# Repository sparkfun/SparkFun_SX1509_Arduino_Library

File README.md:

SparkFun SX1509 IO Expander Breakout Arduino Library
========================================

[*SparkFun SX1509 IO Expander Breakout (SKU)*](https://www.sparkfun.com/products/13601)

Arduino library for the SX1509 16-I/O expander. Capable of driving LEDs - with blink, and breathe functions - or monitoring up to 64 buttons in an 8x8 array.

Are you low on I/O? No problem! The SX1509 Breakout is a 16-channel GPIO expander with an I2C interface – that means with just two wires, your microcontroller can interface with 16 fully configurable digital input/output pins. But the SX1509 can do so much more than just simple digital pin control. It can produce PWM signals, so you can dim LEDs. It can be set to blink or even breathe pins at varying rates. This breakout is similar to a multiplexer or "mux," in that it allows you to get more IO from less pins. And, with a built-in keypad engine, it can interface with up to 64 buttons set up in an 8x8 matrix.

Two headers at the top and bottom of the breakout board function as the input and control headers to the board. This is where you can supply power to the SX1509, and where your I2C signals – SDA and SCL – will terminate. GPIO and power buses are broken out in every-which direction, and configurable jumpers cover most of the rest of the board.

Since the I/O banks can operate between 1.2V and 3.6V (5.5V tolerant) independent of both the core and each other, this device can also work as a level-shifter. The SX1509 breakout makes it easy to prototype so you can add more I/O onto your Arduino or I/O limited controller. We've even spun up an Arduino Library to get you started!

Please be aware that v3 of the library breaks previous version compatiblity on a few things:

* Wire.begin() must be called explicitly within the Arduino sketch before io.begin() is called. This may break code that does not have Wire.begin().
* io.begin() has been expanded to include io.begin(deviceAddress, wirePort, resetPin). This may break code where resetPin was the 2nd argument.

Repository Contents
-------------------

* **/examples** - Example sketches for the library (.ino). Run these from the Arduino IDE.
* **/extras** - Additional documentation for the user. These files are ignored by the IDE.
* **/src** - Source files for the library (.cpp, .h).
* **keywords.txt** - Keywords from this library that will be highlighted in the Arduino IDE.
* **library.properties** - General library properties for the Arduino package manager.

Documentation
--------------

* **[SparkFun SX1509 Breakout Board Hookup Guide](https://learn.sparkfun.com/tutorials/sx1509-io-expander-breakout-hookup-guide)** - SparkFun tutorial demonstrating how to hook up the SX1509 Breakout and use this library.
* **[Installing an Arduino Library Guide](https://learn.sparkfun.com/tutorials/installing-an-arduino-library)** - Basic information on how to install an Arduino library.
* **[Product Repository](https://github.com/sparkfun/SX1509_IO-Expander)** - Main repository (including hardware files) for the SX1509 IO Expander Breakout.

Products that use this Library
---------------------------------

* [BOB-13601](https://www.sparkfun.com/products/13601) - SX1509 16 I/O Breakout Board (v2.0)
* [BOB-11502](https://www.sparkfun.com/products/retired/11502)- (Retired) 16 I/O I2C port expander.

Version History
---------------

* [V_2.0.1](https://github.com/sparkfun/SparkFun_SX1509_Arduino_Library/tree/V_2.0.1) - Version 2.0.1. More user-friendly function calls. Increased clock functionality. More examples. Mostly backwards compatible with older versions.
* [V_1.0.0](https://github.com/sparkfun/SparkFun_SX1509_Arduino_Library/tree/V_1.0.0) - Version 1.0.0

License Information
-------------------

This product is _**open source**_!

The **code** is beerware; if you see me (or any other SparkFun employee) at the local, and you've found our code helpful, please buy us a round!

Please use, reuse, and modify these files as you see fit. Please maintain attribution to SparkFun Electronics and release anything derivative under the same license.

Distributed as-is; no warranty is given.

- Your friends at SparkFun.

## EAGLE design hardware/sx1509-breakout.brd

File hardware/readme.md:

# What Are these Files?
The .sch and .brd files hare are Eagle CAD schematic and PCB design files.

These files were created with Eagle 6.2.0, you'll need Eagle 6.0 or later to open them up. There is a free, lite, version of Eagle available from [cadsoftusa.com](http://www.cadsoftusa.com).

# Board Features

It's just a breakout board for the SX1509, but it does have its fair share of shortcuts.

## Jumpers

There are five surface mount jumpers located on the back side of the board: two to select the I<sup>2</sup>C address and two to enable the VCC1 and VCC2 rails for I/O's 0-7 and 8-15 respectively. And one jumper to disable/enable 10k pull-up resistors.

<div align="center"></div>

All jumpers are set to a default value with a small, exposed trace between the pads. With a semi-sharp exacto blade, these traces should be relatively easy to cut.

In the case of the address jumper, if you cut the trace, you'll need to apply a bubble of solder jumping the middle pad to **one** of the other two edge pads to set the ADDR pins.

### Address Jumpers

These two jumper select the I<sup>2</sup>C address of the SX1509. These jumpers allow you to select the value of the **SX1509's ADDR0 and ADDR1** pins - either VCC (1) or GND (0).

These jumpers both default to GND (0).

A table of possible values is printed on the PCB, but I'll stick it here too.

<table border="1" align="center">
<tr align="center"><td><b>ADDR1</b></td><td><b>ADDR0</b></td><td><b>SX1509 7-bit Address</b></td></b></tr>
<tr align="center"><td>0</td><td>0</td><td>0x3E</td></tr>
<tr align="center"><td>0</td><td>1</td><td>0x3F</td></tr>
<tr align="center"><td>1</td><td>0</td><td>0x70</td></tr>
<tr align="center"><td>1</td><td>1</td><td>0x71</td></tr>
</table>

### I/O Rail Jumpers

If you're looking to take advantage of the SX1509's level-shifting functionality, you may want to use the VCC1 and VCC2 pins. These pins can supply the voltage for I/O pins 0-7 and 8-15 respectively.

**Closed**, these jumpers will **short VCC1 and VCC2 to VCC** (the supply voltage 1.2-3.6V). Open the jumpers and you'll have to connect your own voltage supply. If no supply is tied to VCC1 and VCC2, the I/O pins will not work.

These jumpers **default to closed**, which means both I/O rails are tied to the supply voltage (usually 3.3V).

### Pull-up Resistor Jumpers

The SX1509 Breakout comes with 10k resistors to pull-up the I<sup>2</sup>C lines - SDA and SCL. This jumper ties both of those resistors to VCC.

The middle pad of this three-way jumper is connected to VCC. On either side is a connection to a resistor, which connects on the other end to SDA or SCL. Shorting both jumpers to VCC connects both resistors to VCC. Cutting the jumper creates an open connection on the resistor, basically removing them from the circuit.

By default, both jumpers are shorted, turning the pull-up resistors on. Should your setup require the pull-up resistors not be connected, take an exacto blade to both wire snippets.

## 2x5 Pin Headers

All I/O, power and GND pins are broken out to either side of the breakout in a breadboard-friendly manner. But 16+ wires could create quite a mess upon exiting a breadboard and entering a project. So we also made all of those 16 I/O's ribbon cable compatible.

The two 2x5 headers should mate with our [2x5 Pin Shrouded Headers](https://www.sparkfun.com/products/8506), which could mate with [Ribbon Crimp Connectors](https://www.sparkfun.com/products/10650), which could mate with [10-Wire Ribbon Cable](https://www.sparkfun.com/products/10647)!

Each of the 2x5 headers breakout out 8 I/O pins, a GND pin, and the VCC rail for that set of pins. The pinout of each connector is on the bottom of the board, but check out this picture if the bottom isn't easily visible.

<div align="center"></div>

# License
This project is released as **beerware**. Feel free to use it, with or without attribution, in your own projects. If you find it helpful, buy me a beer (alcoholic or root variety are both fine :) next time we meet up.

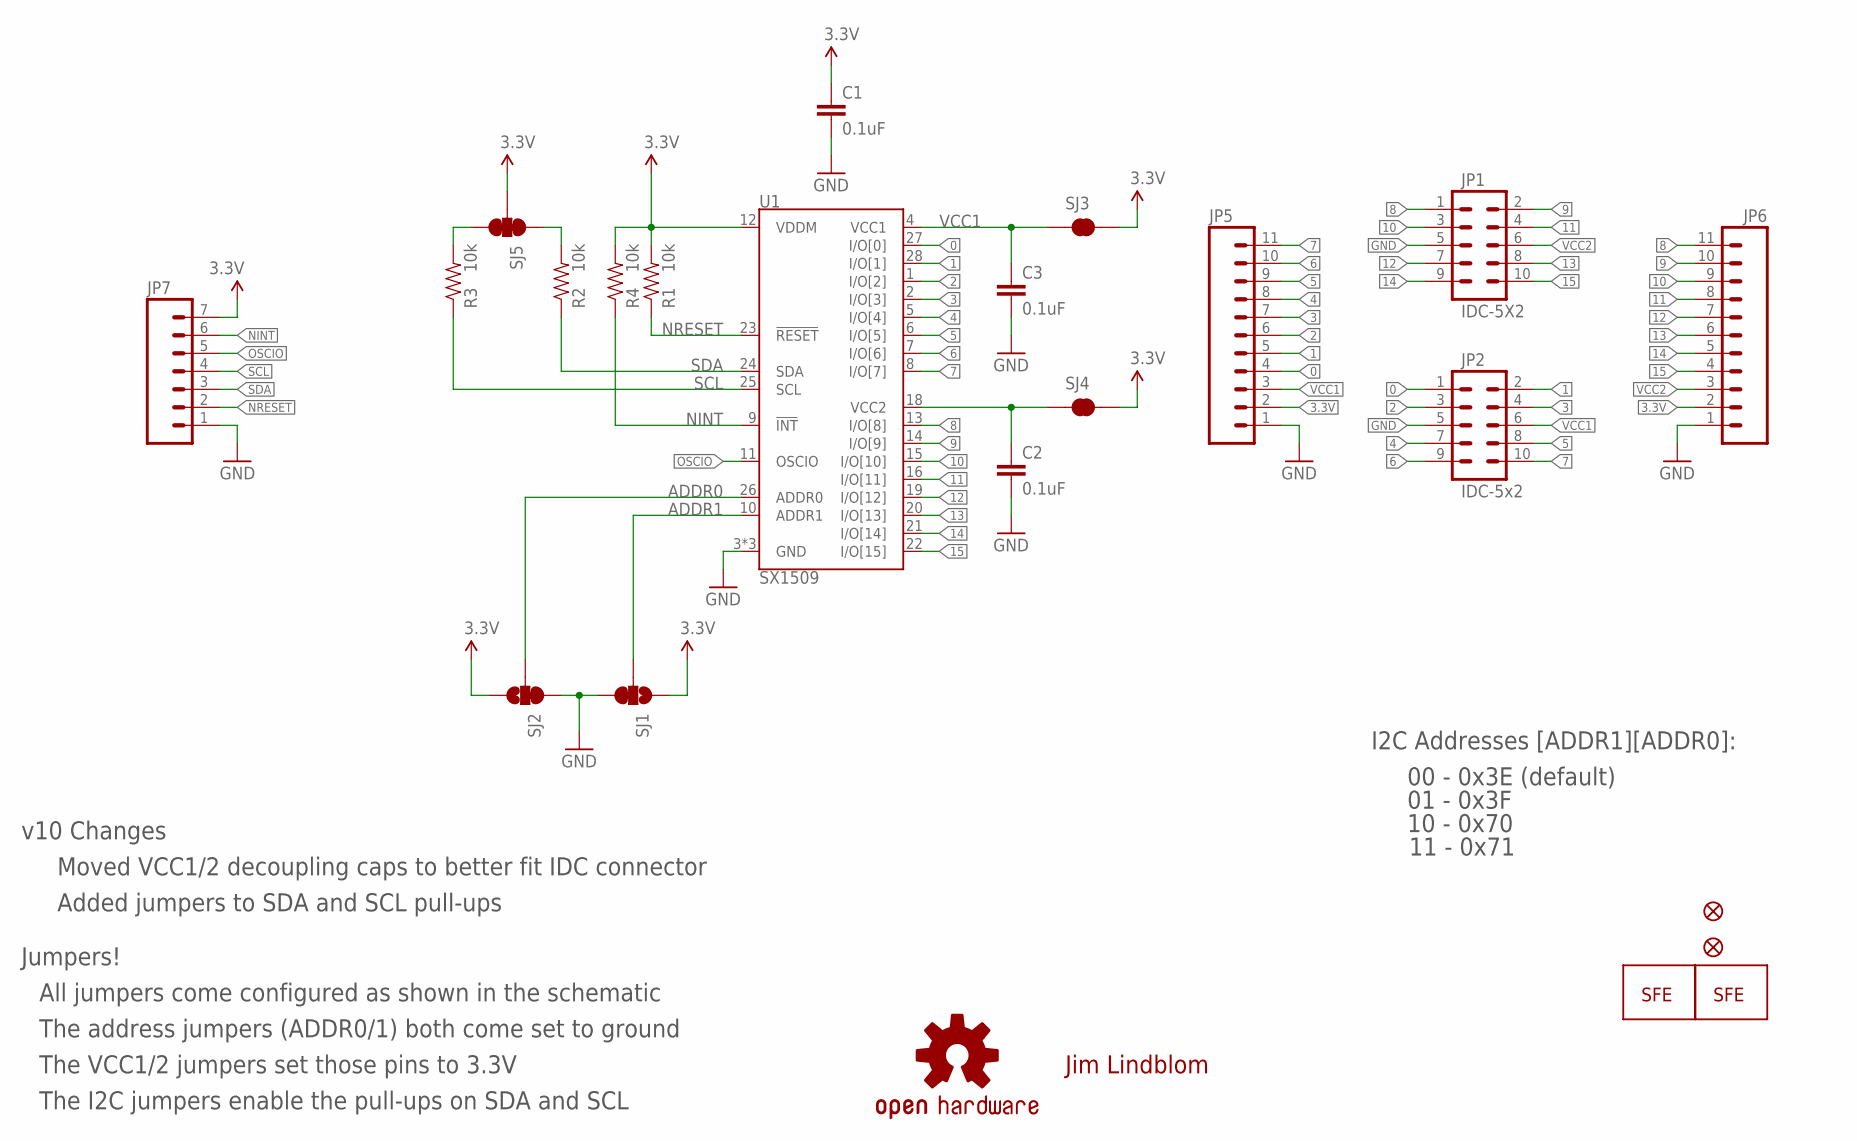
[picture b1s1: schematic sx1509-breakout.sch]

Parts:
C1, C2, C3: 0.1uF; 0402-CAP
JP1: IDC-5X2; 2X5-SHROUDED-NO_SILK
JP2: IDC-5x2; 2X5-SHROUDED-NO_SILK
JP3: LOGO-SFENEW; SFE-NEW-WEBLOGO
JP4: LOGO-SFESK; SFE-LOGO-FLAME
JP5, JP6: M111X11_NO_SILK; 1X11_NO_SILK
JP7: M07; 1X07
JP8, JP9: FIDUCIALUFIDUCIAL; MICRO-FIDUCIAL
R1, R2, R3, R4: 10k; 0402-RES
SJ1, SJ2, SJ5: SOLDERJUMPER_2WAYS; SJ_3
SJ3, SJ4: SOLDERJUMPERNO; SJ_2S-NO
U1: SX1509; QFN-28
U$1: OSHW-LOGOS; OSHW-LOGO-S

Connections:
0: JP2.1, JP5.4, U1.27 (I/O[0])
1: JP2.2, JP5.5, U1.28 (I/O[1])
2: JP2.3, JP5.6, U1.1 (I/O[2])
3: JP2.4, JP5.7, U1.2 (I/O[3])
3.3V: C1.1, JP5.2, JP6.2, JP7.7, R1.2, R4.2, SJ1.1, SJ2.3, SJ3.2, SJ4.2, SJ5.2, U1.12 (VDDM)
4: JP2.7, JP5.8, U1.5 (I/O[4])
5: JP2.8, JP5.9, U1.6 (I/O[5])
6: JP2.9, JP5.10, U1.7 (I/O[6])
7: JP2.10, JP5.11, U1.8 (I/O[7])
8: JP1.1, JP6.11, U1.13 (I/O[8])
9: JP1.2, JP6.10, U1.14 (I/O[9])
10: JP1.3, JP6.9, U1.15 (I/O[10])
11: JP1.4, JP6.8, U1.16 (I/O[11])
12: JP1.7, JP6.7, U1.19 (I/O[12])
13: JP1.8, JP6.6, U1.20 (I/O[13])
14: JP1.9, JP6.5, U1.21 (I/O[14])
15: JP1.10, JP6.4, U1.22 (I/O[15])
ADDR0: SJ2.2, U1.26 (ADDR0)
ADDR1: SJ1.2, U1.10 (ADDR1)
GND: C1.2, C2.2, C3.2, JP1.5, JP2.5, JP5.1, JP6.1, JP7.1, SJ1.3, SJ2.1, U1.3 (GND), U1.17 (GND), U1.29 (GND)
unnamed: R3.2, SJ5.3
unnamed: R2.2, SJ5.1
NINT: JP7.6, R4.1, U1.9 (!INT)
NRESET: JP7.2, R1.1, U1.23 (!RESET)
OSCIO: JP7.5, U1.11 (OSCIO)
SCL: JP7.4, R3.1, U1.25 (SCL)
SDA: JP7.3, R2.1, U1.24 (SDA)
VCC1: C3.1, JP2.6, JP5.3, SJ3.1, U1.4 (VCC1)
VCC2: C2.1, JP1.6, JP6.3, SJ4.1, U1.18 (VCC2)

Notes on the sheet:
Jim Lindblom
Jumpers!
v10 Changes
Moved VCC1/2 decoupling caps to better fit IDC connector
Added jumpers to SDA and SCL pull-ups
All jumpers come configured as shown in the schematic
The address jumpers (ADDR0/1) both come set to ground
The VCC1/2 jumpers set those pins to 3.3V
The I2C jumpers enable the pull-ups on SDA and SCL
I2C Addresses [ADDR1][ADDR0]:
00 - 0x3E (default)
01 - 0x3F
10 - 0x70
11 - 0x71

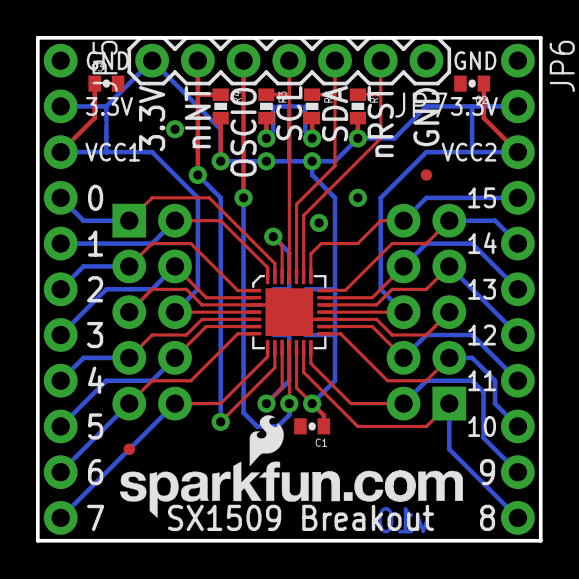
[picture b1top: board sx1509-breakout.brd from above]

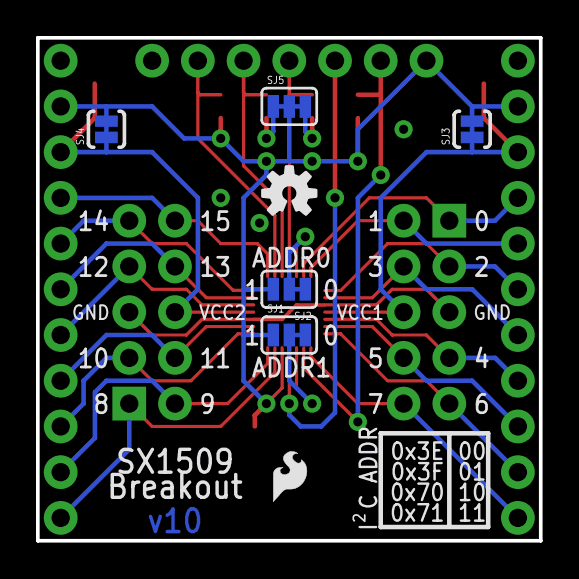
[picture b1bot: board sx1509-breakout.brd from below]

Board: 2 copper layers, 27.9 x 27.9 mm, 23 parts (7 on the bottom side), 29 nets.

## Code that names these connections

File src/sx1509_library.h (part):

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// Inputs:
//		- address: should be the 7-bit address of the SX1509. This should be  
//		 one of four values - 0x3E, 0x3F, 0x70, 0x71 - all depending on what the
//		 ADDR0 and ADDR1 pins ar se to. This variable is required.
//		- resetPin: This is the Arduino pin tied to the SX1509 RST pin. This
//		 pin is optional. If not declared, the library will attempt to
//		 software reset the SX1509.
//		- interruptPin: This is the Arduino pin tied to the SX1509 active-low
//		 interrupt output. Only necessary if you're planning on using
//		 the interrupt capabilities.
//		- oscillatorPin: This is the Arduino pin tied to the SX1509's OSCIO 
//		 pin. This pin can be an output or an input. This parameter is optional.
// -----------------------------------------------------------------------------
	sx1509Class(byte address, byte resetPin = 255, 
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// -----------------------------------------------------------------------------
// sync(void): this function resets the PWM/Blink/Fade counters, syncing any 
//		blinking LEDs. Bit 2 of REG_MISC is set, which alters the functionality 
//		of the nReset pin. The nReset pin is toggled low->high, which should 
//		reset all LED counters. Bit 2 of REG_MISC is again cleared, returning 
//		nReset pin to POR functionality
// -----------------------------------------------------------------------------
	void sync(void);
	
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//
//	Inputs:
//	- oscSource: Choose either internal 2MHz oscillator or an external signal 
//		applied to the OSCIO pin.
//		- INTERNAL_CLOCK and EXTERNAL_CLOCK are defined in the header file.
//			Use those.
//		- This value defaults to internal.
//	- oscPinFunction: Allows you to set OSCIO as an input or output.
//		- You can use Arduino's INPUT, OUTPUT defines for this value
//		- This value defaults to input
//	- oscFreqOut: If oscio is configured as an output, this will set the output 
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
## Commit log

2012-11-14 Hardware initial commit
    and a readme
2012-11-14 Library initial commit
    Working example code for init, pinDir, writePin, and readPin.
2012-11-15 Added much LED Driver functionality
    New Functions: ledDriverInit, pwm, blink, sync
    New example to demo LED driver
    Renamed simple example
2012-11-16 Debounce, interrupt and clock config functions
    Added a new example sx1509_interruptDebounce.ino
    Fixed some directory structure with examples
    Typo on a register in sx1509_registers.h
    Added keywords.txt (doesn't seem to work...hmm)
2012-11-20 Keypad engine functions and arduino example
    Added keypad(byte rows, byte columns, byte sleepTime, byte scanTime) and
    nsigned int readKeyData() to sx1509Class
2012-12-13 Comments! Licenses!
    Moved function explanation comments to the sx1509_library.h.
    Slight changes to the digitalReadWrite example.
2013-01-03 Readme goodness.
    Also removed a duplicate sx1509_ledDriver.ino and its folder.
2013-01-04 Some hardware readme action.
2013-03-08 purging HTML, adding license info and standard image/link setup
2015-04-24 Revising file structure to match Arduino 1.6 standards.
2015-04-24 Revising README.md
2015-09-08 Adding sink flag to ledDriverInit
2015-09-08 Updating file and library names to match SparkFun guidelines
2015-09-08 Fixing library name in properties file (no slashes allowed)
2015-09-21 Updating to version 2.0 - more user-friendly
    - Made most functions more user friendly.
    - digitalWrite, pinMode, and other standard Arduino function calls are
    used.
    - Should remain mostly backwards compatible.
    - blink and breathe functions now try to estimate millisecond durations
    - Improved clock control
2015-09-23 Updating README for hardware v20
2015-09-25 Reverting library name
2015-09-25 Pointing to tag V_2.0.1
2017-06-25 Remove unused variable in function readBytes
    The results of Wire.read() are directly placed into an array passed as a function variable. The variable may have been used previously, but now is not.
2017-06-25 Update SparkFunSX1509.cpp
    The results of Wire.read() are directly placed into an array passed as a function variable. The variable may have been used previously, but now is not.
2017-06-25 Issue #2
    No need to wait for data after Wire.requestFrom() #2
2018-07-15 Correct case of reference link in keywords.txt
    The third field of keywords.txt is used to provide Arduino Language/Libraries Reference links, which are accessed from the Arduino IDE by highlighting the keyword and then selecting "Find in Referenc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
    Reference:
    https://github.com/arduino/Arduino/wiki/Arduino-IDE-1.5:-Library-specification#keywordstxt-format
2020-07-18 Adapted for use with TwoWire (NOT BACKWARDS COMPATIBLE)
    Seems like bad practise to Wire.begin() inside library, so it's been removed.
2020-10-28 Added initialLevel parameter to pinMode() and pinDir()
2021-03-30 Added return boolean to write operations
2021-03-31 Added read methods returning success boolean
2021-09-02 Include return value of Wire.endTransmission into result of write*() methods
2021-10-13 Update all examples: Add Wire.begin, 115200bps default, link to library.
2021-10-13 Make device address first var on begin() to match old code.
2021-10-14 VSC white space changes
2021-10-14 Replace lone Wire.read() with _i2cPort->
2021-10-14 Remove timeout checking
    Vestige from other branch. No need: https://github.com/Koepel/How-to-use-the-Arduino-Wire-library/wiki/Common-mistakes
2021-10-14 Replace byte casts with uint8_t
2021-10-14 Update readme and lib properties
2021-10-14 Update writeBytes to write buffer instead of byte wise.
2021-10-14 Replace ints with uint16_t. Define I2C_ERROR_OK as needed.
2021-10-14 Update comments on examples to reflect 115200bps.
2021-11-20 Commented RECEIVE_TIMEOUT_VALUE as variable seems unused
    The variables 'RECEIVE_TIMEOUT_VALUE' in SX1509::readByte & SX1509::readWord seem to be unused. Commented.
2021-11-28 Bug Fix
2022-01-29 fixed LED driver clock setting in function ledDriverInit()
2022-01-29 fixed issue in setting LED driver frequency in function ledDriverInit()
2022-02-26 Create DigitalReadWriteCombined.ino
    Add updated example code and serial output from Jim's tutorial based on v3 of the library. The example combines the digitalRead() and digitalWrite().
2022-04-04 Fix reset to use system definition of digital write
2023-06-20 fixed typecasting error in time periods in calculateSlopeRegister and calculateLEDTRegister
2023-11-01 Changes to fix multiple Issues
2023-11-01 Update ledDriverInit() to call configClock()
2023-11-01 Minor fix to SparkFunSX1509.h
2023-11-21 Fixes issue in SX1509::readWord(uint8_t, uint16_t *)
    Existing implementation accessed memory it shouldn't, and didn't write both values to the target uint16_t.
2025-04-28 v3.0.6

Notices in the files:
src/sx1509_library.h:
license: Beerware. Feel free to use it, with or without attribution, in
parts and their libraries:
SparkFun-DigitalIC: Licensing: CC v3.0 Share-Alike You are welcome to use this library for commercial purposes.
SparkFun-Aesthetics: Released under the Creative Commons
SparkFun-Aesthetics: http://creativecommons.org/licenses/by-sa/3.0
